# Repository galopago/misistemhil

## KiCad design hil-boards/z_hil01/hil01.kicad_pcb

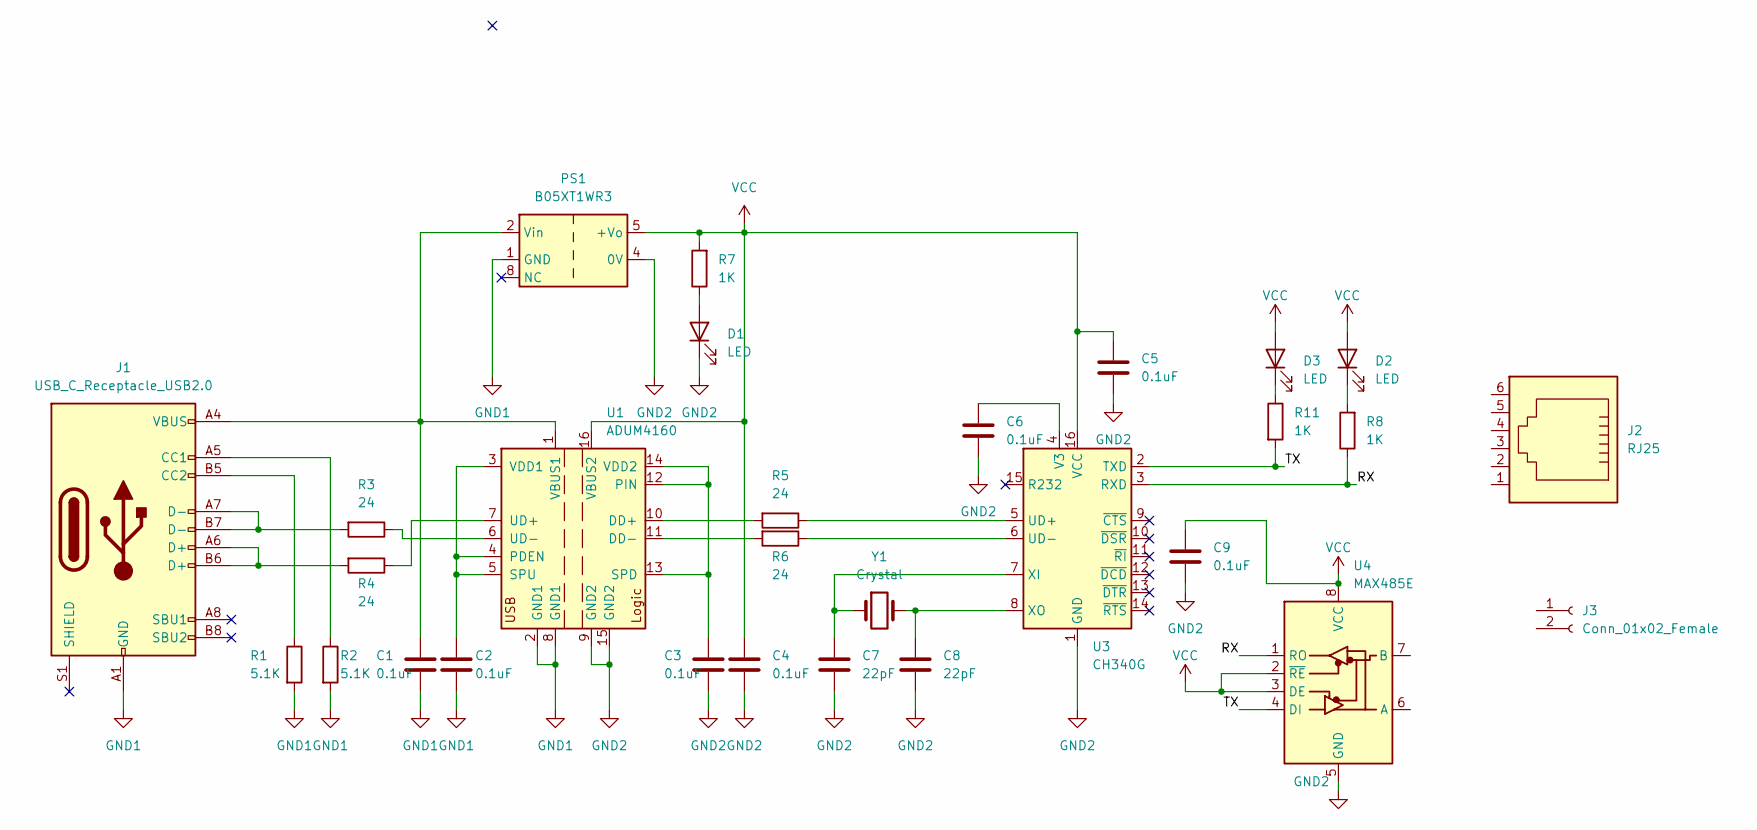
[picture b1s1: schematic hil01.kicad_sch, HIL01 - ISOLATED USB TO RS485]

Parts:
C1, C2, C3, C4, C5, C6, C9: 0.1uF; C_0805_2012Metric_Pad1.18x1.45mm_HandSolder
C7, C8: 22pF; C_0805_2012Metric_Pad1.18x1.45mm_HandSolder
D1, D2, D3: LED; D_0805_2012Metric_Pad1.15x1.40mm_HandSolder
J1: USB_C_Receptacle_USB2.0; USB_C_Receptacle_HRO_TYPE-C-31-M-12
J2: RJ25; RJ25_Wayconn_MJEA-660X1_Horizontal
J3: Conn_01x02_Female; TerminalBlock_Kefa_1x02_P6.35mm_Horizontal
PS1: B05XT1WR3; Converter_DCDC_Mornsun_B05_XT_1WR3_SMD
R1, R2: 5.1K; R_0805_2012Metric_Pad1.20x1.40mm_HandSolder
R3, R4, R5, R6: 24; R_0805_2012Metric_Pad1.20x1.40mm_HandSolder
R7, R8, R11: 1K; R_0805_2012Metric_Pad1.20x1.40mm_HandSolder
U1: ADUM4160; SOIC-16W_7.5x10.3mm_P1.27mm
U3: CH340G; SOIC-16_3.9x9.9mm_P1.27mm
U4: MAX485E; SO-8_3.9x4.9mm_P1.27mm
Y1: Crystal; Crystal_SMD_HC49-SD_HandSoldering_Compact

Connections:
/RX: R8.1, U3.3 (RXD), U4.1 (RO)
/TX: R11.2, U3.2 (TXD), U4.4 (DI)
GND1: C1.2, C2.2, J1.A1 (GND), J1.A12 (GND), J1.B1 (GND), J1.B12 (GND), PS1.1 (GND), R1.2, R2.2, U1.2 (GND1), U1.8 (GND1)
GND2: C3.2, C4.2, C5.2, C6.2, C7.2, C8.2, C9.2, D1.1 (K), PS1.4 (0V), U1.9 (GND2), U1.15 (GND2), U3.1 (GND), U4.5 (GND); also elsewhere on the board
unnamed: C1.1, J1.A4 (VBUS), J1.A9 (VBUS), J1.B4 (VBUS), J1.B9 (VBUS), PS1.2 (Vin), U1.1 (VBUS1)
unnamed: C2.1, U1.3 (VDD1), U1.4 (PDEN), U1.5 (SPU)
unnamed: C3.1, U1.12 (PIN), U1.13 (SPD), U1.14 (VDD2)
unnamed: C6.1, U3.4 (V3)
unnamed: C7.1, U3.7 (XI), Y1.1
unnamed: C8.1, U3.8 (XO), Y1.2
unnamed: D1.2 (A), R7.1
unnamed: D2.1 (K), R8.2
unnamed: D3.1 (K), R11.1
unnamed: J1.A5 (CC1), R2.1
unnamed: J1.A6 (D+), J1.B6 (D+), R4.2
unnamed: J1.A7 (D-), J1.B7 (D-), R3.2
unnamed: J1.B5 (CC2), R1.1
unnamed: R3.1, U1.6 (UD-)
unnamed: R4.1, U1.7 (UD+)
unnamed: R5.1, U3.5 (UD+)
unnamed: R5.2, U1.10 (DD+)
unnamed: R6.1, U3.6 (UD-)
unnamed: R6.2, U1.11 (DD-)
VCC: C4.1, C5.1, C9.1, D2.2 (A), D3.2 (A), PS1.5 (+Vo), R7.2, U1.16 (VBUS2), U3.16 (VCC), U4.2 (~RE), U4.3 (DE), U4.8 (VCC)

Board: 2 copper layers, 31 parts (0 on the bottom side), 24 nets, no tracks yet.

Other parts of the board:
R12, R13: 100; R_0805_2012Metric_Pad1.20x1.40mm_HandSolder

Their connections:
GND2: R12.2, R13.2; also elsewhere on the board
